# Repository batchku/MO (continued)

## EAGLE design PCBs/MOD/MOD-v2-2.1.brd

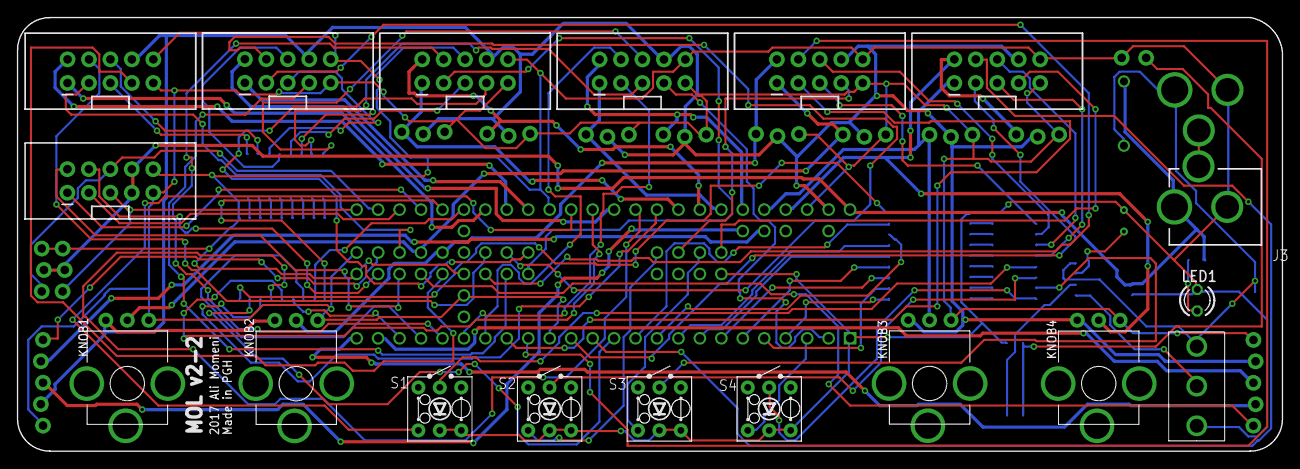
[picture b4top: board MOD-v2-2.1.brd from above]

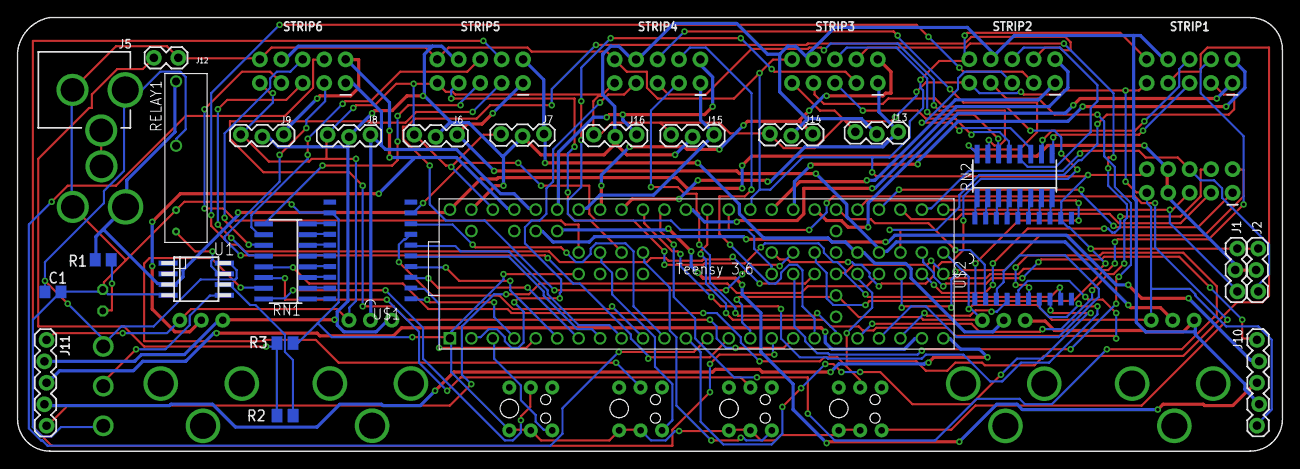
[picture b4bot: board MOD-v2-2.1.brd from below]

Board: 2 copper layers, 149.8 x 51.3 mm, 43 parts (25 on the bottom side), 106 nets.

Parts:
C1: 10uF; C0805
J1: SERVO1; 1X03_LOCK@1
J2: SERVO2; 1X03_LOCK@1
J3: RPi; DCJACK_2MM_PTH
J4: ACTUATORS; 2X5-SHROUDED_LOCK
J5: Battery; DCJACK_2MM_PTH
J6, J13: AN5; 1X03_LOCK
J7, J14: AN6; 1X03_LOCK
J8, J15: AN7; 1X03_LOCK
J9, J16: AN8; 1X03_LOCK
J10: JOY1; 1X05_LOCK
J11: JOY2; 1X05_LOCK
J12: RPi-Shutdown; 1X02_LOCK
KNOB1, KNOB2, KNOB3, KNOB4: TRIM-PCB-9MM
LED1: LED3MM
R1: 330; M0805
R2: 2.2K; M0805
R3: 3.3K; M0805
RELAY1: RELAY-OMRON-G6DN; G6DN-1A
RN1, RN2: SO16
S1, S2, S3, S4: SW-LEDPTH; SWITCH_TR2-MOMENTARY-LED
STRIP1, STRIP2, STRIP3, STRIP4, STRIP5, STRIP6: 2X5-SHROUDED_LOCK
SW2: 500SSP1S2M2QEA; SWITCH_SPDT_500SSP1S2M2QEA
TEENSY: TEENSY3_6-ALI_NO-USB-HOST; TEENSY3-6_NO-USB-HOST
U1: ATTINY85
U$1, U$2: A2982; SOIC20

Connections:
+3V3: J4.9, J6.1, J7.1, J8.1, J9.1, J10.1, J11.1, J13.1, J14.1, J15.1, J16.1, KNOB1.1, KNOB2.1, KNOB3.1, KNOB4.1, STRIP1.9, STRIP2.9, STRIP3.9, STRIP4.9, STRIP5.9, STRIP6.9, TEENSY.3V3(1), TEENSY.3V3(2), TEENSY.3V3(3), TEENSY.3V3(4)
+5V: J1.2, J2.2, J3.PWR, J4.7, J4.8, R1.1, RELAY1.8, TEENSY.VIN, U1.3
+5V-BATTERY: C1.1, J5.PWR, RELAY1.5, SW2.1, U1.8
AGND: J6.2, J7.2, J8.2, J9.2, J10.2, J11.2, J13.2, J14.2, J15.2, J16.2, KNOB1.3, KNOB2.3, KNOB3.3, KNOB4.3, STRIP1.8, STRIP2.8, STRIP3.8, STRIP4.8, STRIP5.8, STRIP6.8, TEENSY.AGND
AN1: STRIP1.1, TEENSY.39
AN2: STRIP1.2, TEENSY.DAC0
AN3: STRIP2.1, TEENSY.DAC1
AN4: STRIP2.2, TEENSY.15
AN5: J13.3, STRIP3.1, TEENSY.18
AN6: J14.3, STRIP3.2, TEENSY.19
AN7: J15.3, STRIP4.1, TEENSY.20
AN8: J16.3, STRIP4.2, TEENSY.21
AN9: J6.3, KNOB1.2, STRIP5.1, TEENSY.49
AN10: J7.3, KNOB2.2, STRIP5.2, TEENSY.50
AN11: J8.3, KNOB3.2, STRIP6.1, TEENSY.22
AN12: J9.3, KNOB4.2, STRIP6.2, TEENSY.23
B1: STRIP1.3, TEENSY.48
B2: STRIP1.4, TEENSY.51
B3: STRIP2.3, TEENSY.42
B4: STRIP2.4, TEENSY.52
B5: STRIP3.3, TEENSY.40
B6: STRIP3.4, TEENSY.28
B7: STRIP4.3, TEENSY.27
B8: STRIP4.4, TEENSY.26
B9: STRIP5.3, TEENSY.25
B10: STRIP5.4, TEENSY.24
B11: STRIP6.3, TEENSY.12
B12: STRIP6.4, TEENSY.11
B13: S1.3, TEENSY.13
B14: S2.3, TEENSY.54
B15: S3.3, TEENSY.56
B16: S4.3, TEENSY.1
GND: C1.2, J1.1, J2.1, J3.GND, J4.10, J5.GND, J12.2, LED1.K, R3.2, RELAY1.2, S1.1, S1.C, S2.1, S2.C, S3.1, S3.C, S4.1, S4.C, STRIP1.10, STRIP2.10, STRIP3.10, STRIP4.10, STRIP5.10, STRIP6.10, SW2.3, TEENSY.G0, TEENSY.G1, TEENSY.G2, TEENSY.G3, TEENSY.G6, U1.4, U$1.12, U$2.12
GNDBREAK: J3.GNDBREAK, J5.GNDBREAK
JOYB1: J10.5, TEENSY.47
JOYB2: J11.5, TEENSY.44
JOYH1: J10.3, TEENSY.A11
JOYH2: J11.3, TEENSY.31
JOYV1: J10.4, TEENSY.A10
JOYV2: J11.4, TEENSY.32
LED1: STRIP1.7, TEENSY.43
LED2: STRIP2.7, TEENSY.41
LED3: STRIP3.7, TEENSY.53
LED4: STRIP4.7, TEENSY.0
LED5: STRIP5.7, TEENSY.55
LED6: STRIP6.7, TEENSY.57
M_INA: J4.2, TEENSY.45
M_INB: J4.4, TEENSY.46
M_PWMA: J4.1, TEENSY.36
M_PWMB: J4.3, TEENSY.35
unnamed: LED1.A, R1.2
unnamed: SW2.2, U1.5
unnamed: RELAY1.1, U1.7
unnamed: J12.1, R2.2, R3.1
unnamed: RN1.8, U$1.13
unnamed: RN1.7, U$1.14
unnamed: RN1.6, U$1.15
unnamed: RN1.5, U$1.16
unnamed: RN1.4, U$1.17
unnamed: RN1.3, U$1.18
unnamed: RN1.2, U$1.19
unnamed: RN1.1, U$1.20
unnamed: RN2.1, U$2.20
unnamed: RN2.2, U$2.19
unnamed: RN2.3, U$2.18
unnamed: RN2.4, U$2.17
unnamed: RN2.5, U$2.16
unnamed: RN2.6, U$2.15
unnamed: RN2.7, U$2.14
unnamed: RN2.8, U$2.13
PI-REST: R2.1, U1.6
PWM1: TEENSY.8, U$1.7
PWM2: TEENSY.9, U$1.8
PWM3: TEENSY.6, U$1.5
PWM4: TEENSY.7, U$1.6
PWM5: TEENSY.4, U$1.4
PWM6: TEENSY.5, U$1.3
PWM7: TEENSY.2, U$1.1
PWM8: TEENSY.3, U$1.2
PWM9: TEENSY.17, U$2.7
PWM10: TEENSY.10, U$2.8
PWM11: TEENSY.16, U$2.6
PWM12: TEENSY.14, U$2.5
PWM13: TEENSY.30, U$2.4
PWM14: TEENSY.29, U$2.3
PWM15: TEENSY.38, U$2.2
PWM16: TEENSY.37, U$2.1
PWM_1: RN2.9, STRIP1.5
PWM_2: RN2.10, STRIP1.6
PWM_3: RN2.11, STRIP2.5
PWM_4: RN2.12, STRIP2.6
PWM_5: RN2.13, STRIP3.5
PWM_6: RN2.14, STRIP3.6
PWM_7: RN2.15, STRIP4.5
PWM_8: RN2.16, STRIP4.6
PWM_9: RN1.9, STRIP5.5
PWM_10: RN1.10, STRIP5.6
PWM_11: RN1.12, STRIP6.5
PWM_12: RN1.11, STRIP6.6
PWM_13: RN1.13, S1.A
PWM_14: RN1.14, S2.A
PWM_15: RN1.15, S3.A
PWM_16: RN1.16, S4.A
S1: J1.3, J4.5, TEENSY.33
S2: J2.3, J4.6, TEENSY.34
V+: U$1.9, U$2.9
